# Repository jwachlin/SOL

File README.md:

# SOL
Long-term solar intensity sensing

People considering a photovoltaic installation on their property should be able to make a data-driven decision about the viability of such a system. While projects such as Google's Project Sunroof can provide large-scale estimates of solar intensity from satellite images, SOL will be able to provide data that incorporates local effects such as roof slope and direction, tree cover, or obstruction from nearby buildings.

See project logs for SOL at the Hackaday project page: https://hackaday.io/project/158984-sol-long-term-solar-intensity-sensing

R2 included a variety of upgrades to lower cost and improve performance:

- ADC with PGA allows better measurement accuracy (ESP32 ADC is highly nonlinear)
- Temperature sensor added (ESP32 internal temperature sensor has very poor performance)
- RTC added for accurate time monitoring without connecting to network
- Smaller PCB with smaller battery (14500 battery)
- Fixed dimensions and location of mounting hole (V1 didn't fit well in case)
- Easier programming by moving required pins to pin headers

However, R2 had some issues:

- Mistake on trace routing held temperature sensor output to ground, making it not work
- Forgot to add load capacitors on RTC crystal, so RTC does not work
- PCB vias not covered with soldermask underneath battery connectors, which would cause shorts
- The charger IC has a large pad underneath it, which was not included in its Eagle part
- The battery silkscreen was left on top of the PCB, when it should have been on the bottom. Not a functional issue, since battery connectors can be attached through either side
- Decoupling capacitor was not put near the ADC, when it should have been. The ADC still seems to work fine, but this should still be fixed

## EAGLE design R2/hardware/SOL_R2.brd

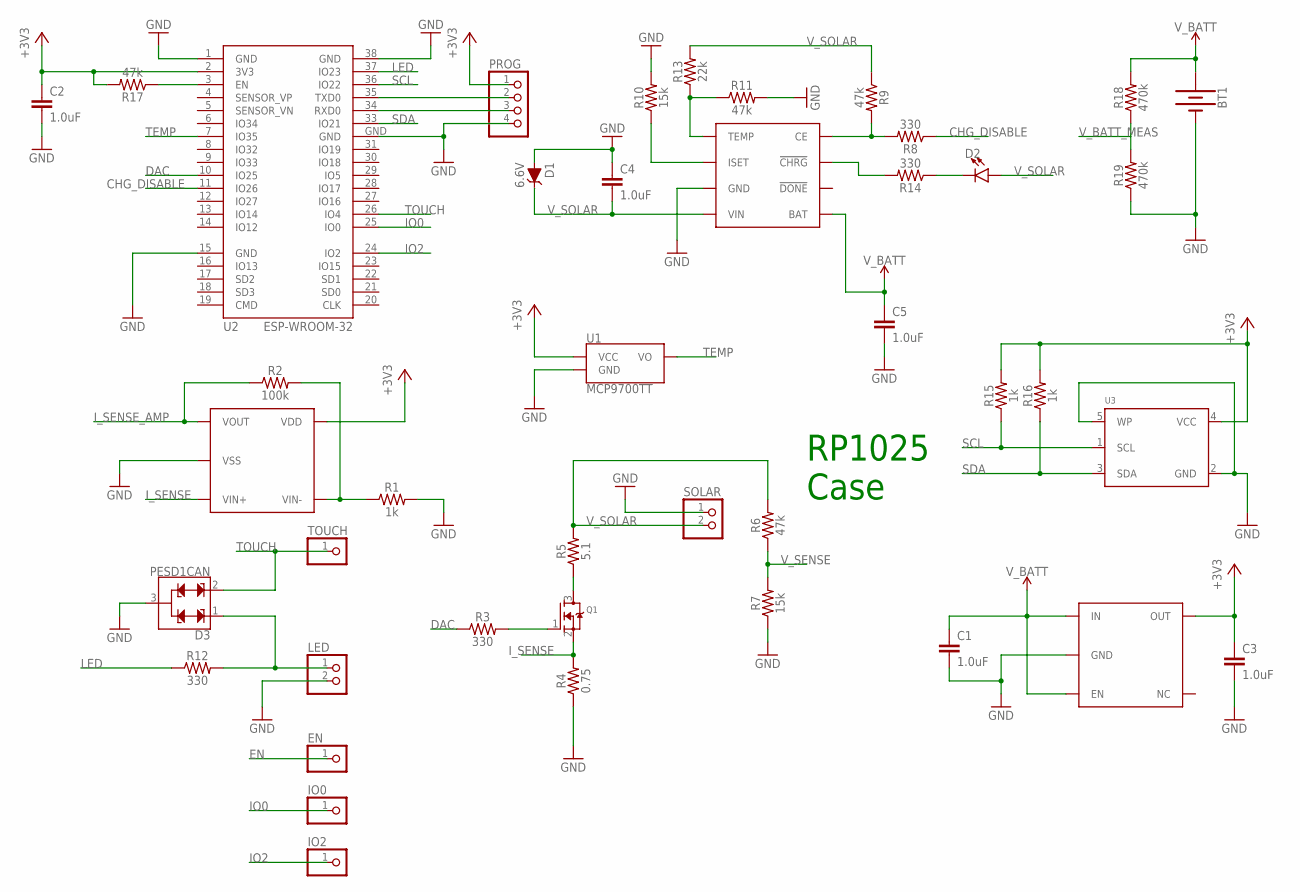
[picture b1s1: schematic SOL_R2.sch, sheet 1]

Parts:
BT1: BATTERY-AA
C1, C2, C3, C4, C5: 1.0uF; 0805
D1: 6.6V; SOD-323
D2: LED0603; LED-0603
D3: PESD1CAN; SOT23-3
EN: PINHD-1X1; 1X01
IO0, IO2: PINHD-1X1; 1X01
LED: PINHD-1X2; 1X02
PROG: PINHD-1X4; 1X04
Q1: MOSFET-NREFLOW; SOT23-R
R1, R15, R16: 1k; 0603
R2: 100k; 0603
R3, R8, R12, R14: 330; 0603
R4: 0.75; 0805
R5: 5.1; 0603
R6, R9, R11, R17: 47k; 0603
R7, R10: 15k; 0603
R13: 22k; 0603
R18, R19: 470k; 0603
SOLAR: PINHD-1X2; 1X02
TOUCH: PINHD-1X1; 1X01
U1: MCP9700TT; SOT23-3
U2: ESP-WROOM-32
U3: EEPROM_I2C_MCP24AA32; SOT23-5
U5: MCP6001; SOT23-5L
U6: TLV755; SOT23-DBV
U7: DIO5158XM8; MSOP8

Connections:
+3V3: C2.1, C3.1, PROG.1, R15.2, R16.2, R17.2, U1.1 (VCC), U2.2 (3V3), U3.4 (VCC), U5.5 (VDD), U6.5 (OUT); also elsewhere on the board
CHG_DISABLE: R8.1, U2.11 (IO26)
DAC: R3.1, U2.10 (IO25)
EN: EN.1, R17.1, U2.3 (EN)
GND: BT1.GND@1 (-), C1.2, C2.2, C3.2, C4.1, C5.2, D1.A, D3.3, LED.2, PROG.4, R1.2, R4.1, R7.1, R10.2, R11.2, R19.1, SOLAR.1, U1.3 (GND), U2.1 (GND), U2.15 (GND), U2.38 (GND), U2.GND, U3.2 (GND), U3.5 (WP), U5.2 (VSS), U6.2 (GND), U7.3 (GND); also elsewhere on the board
IO0: IO0.1, U2.25 (IO0)
IO2: IO2.1, U2.24 (IO2)
I_SENSE: Q1.2 (S), R4.2, U5.3 (VIN+)
I_SENSE_AMP: R2.1, U5.1 (VOUT); also elsewhere on the board
LED: R12.1, U2.37 (IO23)
unnamed: R10.1, U7.2 (ISET)
unnamed: D3.1, LED.1, R12.2
unnamed: R11.1, R13.1, U7.1 (TEMP)
unnamed: Q1.1 (G), R3.2
unnamed: R1.1, R2.2, U5.4 (VIN-)
unnamed: Q1.3 (D), R5.1
unnamed: R8.2, R9.2, U7.8 (CE)
unnamed: R14.2, U7.7 (!CHRG!)
unnamed: D2.C, R14.1
RXD: PROG.3, U2.34 (RXD0)
SCL: R15.1, U2.36 (IO22), U3.1 (SCL); also elsewhere on the board
SDA: R16.1, U2.33 (IO21), U3.3 (SDA); also elsewhere on the board
TEMP: U1.2 (VO), U2.7 (IO35)
TOUCH: D3.2, TOUCH.1, U2.26 (IO4)
TXD: PROG.2, U2.35 (TXD0)
V_BATT: BT1.PWR@1 (+), C1.1, C5.1, R18.2, U6.1 (IN), U6.3 (EN), U7.5 (BAT)
V_BATT_MEAS: R18.1, R19.2; also elsewhere on the board
V_SENSE: R6.1, R7.2; also elsewhere on the board
V_SOLAR: C4.2, D1.C, D2.A, R5.2, R6.2, R9.1, R13.2, SOLAR.2, U7.4 (VIN)

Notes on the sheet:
RP1025 Case

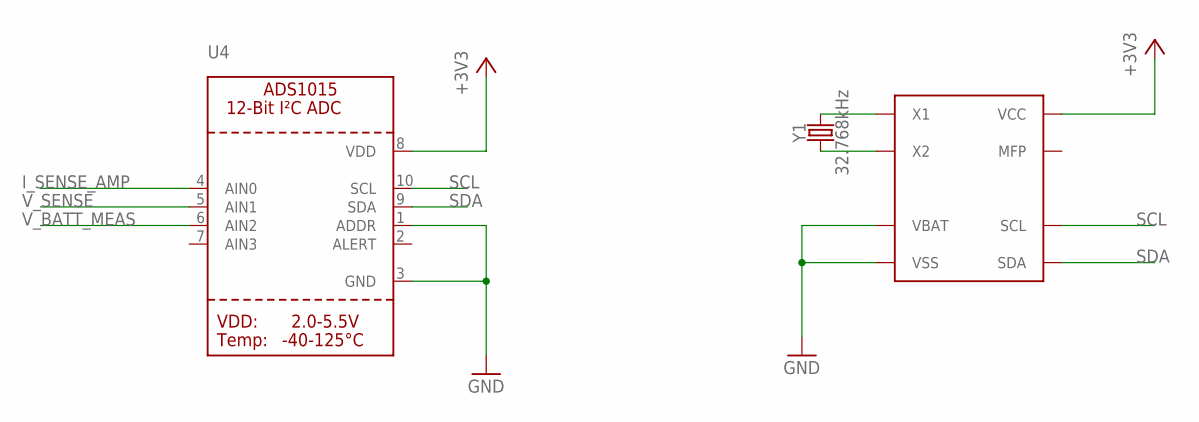
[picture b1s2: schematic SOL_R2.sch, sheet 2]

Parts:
U4: ADC_ADS1015; MSOP10
U8: MCP7940; MSOP8
Y1: 32.768kHz; CRYSTAL-SMD-3.2X1.5MM

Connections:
+3V3: U4.8 (VDD), U8.8 (VCC); also elsewhere on the board
GND: U4.1 (ADDR), U4.3 (GND), U8.3 (VBAT), U8.4 (VSS); also elsewhere on the board
I_SENSE_AMP: U4.4 (AIN0); also elsewhere on the board
unnamed: U8.1 (X1), Y1.P$2 (2)
unnamed: U8.2 (X2), Y1.P$1 (1)
SCL: U4.10 (SCL), U8.6 (SCL); also elsewhere on the board
SDA: U4.9 (SDA), U8.5 (SDA); also elsewhere on the board
V_BATT_MEAS: U4.6 (AIN2); also elsewhere on the board
V_SENSE: U4.5 (AIN1); also elsewhere on the board

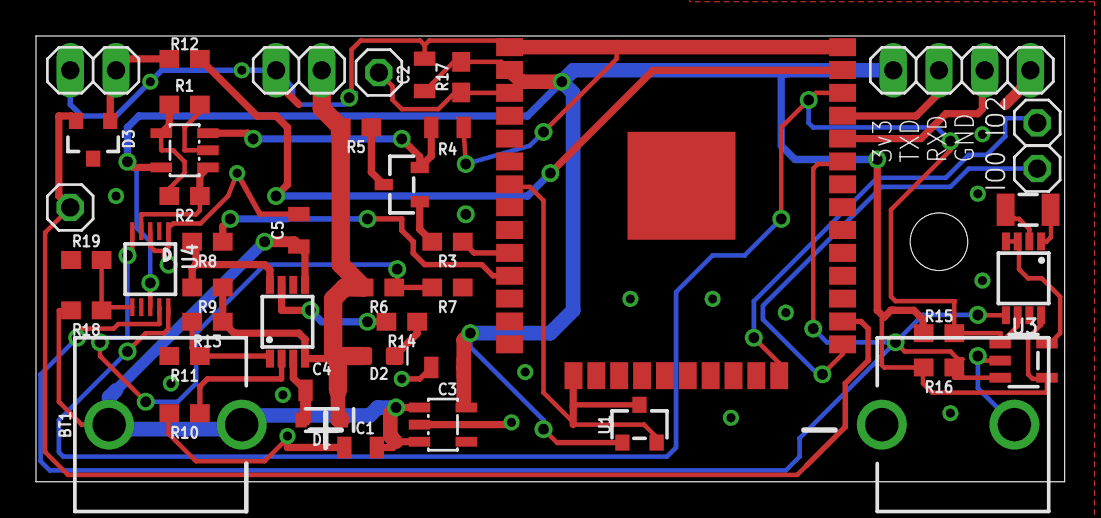
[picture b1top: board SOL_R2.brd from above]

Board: 2 copper layers, 57.1 x 24.8 mm, 45 parts (0 on the bottom side), 31 nets.

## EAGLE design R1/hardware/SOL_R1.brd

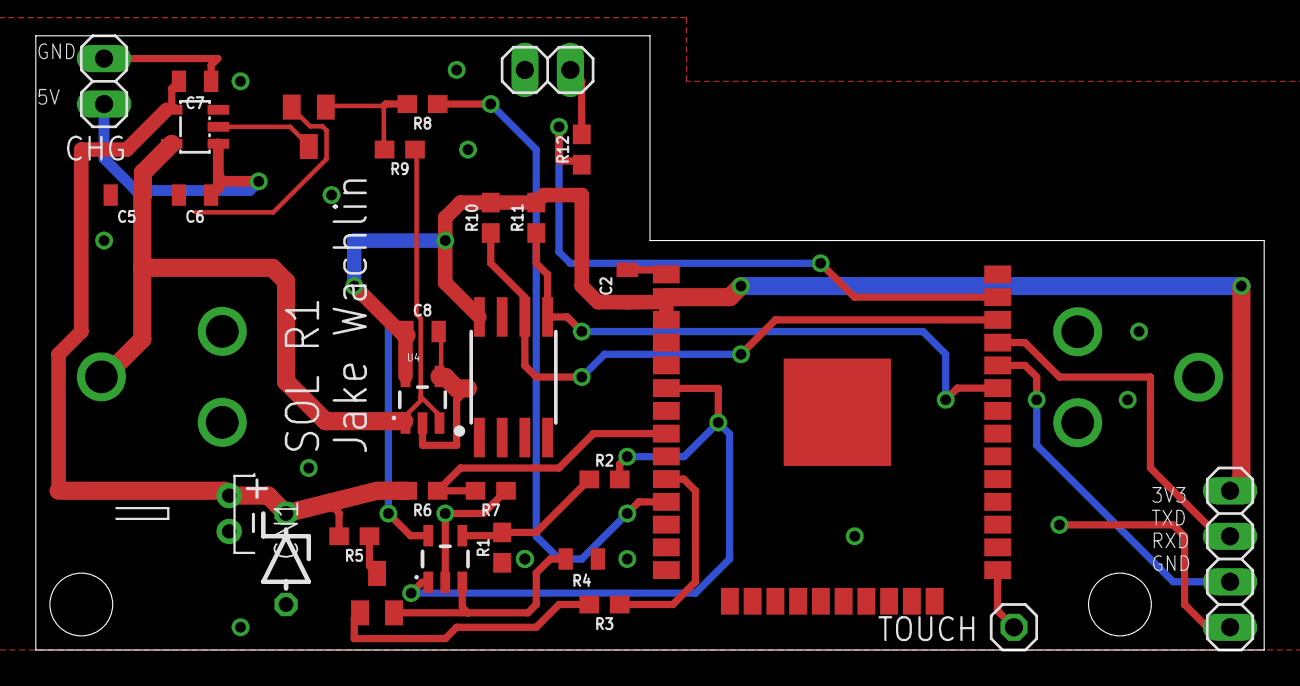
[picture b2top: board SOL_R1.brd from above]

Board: 2 copper layers, 68.6 x 34.3 mm, 31 parts (1 on the bottom side), 22 nets.

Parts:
BT1: BATTERY_18650-HOLDER
C2, C5, C6, C7, C8: 1.0uF; 0805
CHG: 1X02
CN1: JST-PH-2-THM-RA
D2: 7.5V; ZDIO-5
IC1: MAX1555; SOT23-5L
LED: 1X02
PROG: 1X04
Q2, Q3: SOT23
R1: 1k; 0603
R2: 100k; 0603
R3, R8, R12: 330; 0603
R4: 0.75; 0805
R5: 5.1; 0603
R6, R9: 47k; 0603
R7: 15k; 0603
R10, R11: 4.7k; 0603
TOUCH: 1X01
U2: ESP-WROOM-32
U3: I2C EEPROM; SO08-EIAJ
U4: 3.3V/150mA; SOT23-5
U$1: OPA344; SOT23-5

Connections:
+3V3: C2.1, C8.1, PROG.1, R10.2, R11.2, U2.2, U2.3, U3.8, U4.5, U$1.5
+5V: C6.1, CHG.1, IC1.1
CHG_DISABLE: R8.1, U2.11
DAC: R3.1, U2.10
GND: BT1.GND@1, C2.2, C5.2, C6.2, C7.1, C8.2, CHG.2, CN1.2, D2.A, LED.2, PROG.4, Q2.2, R1.1, R4.1, R7.1, U2.1, U2.15, U2.38, U2.GND, U3.1, U3.2, U3.3, U3.4, U3.7, U4.2, U4.4, U$1.2
I_SENSE: Q3.2, R4.2, U$1.3
I_SENSE_AMP: R2.2, U2.6, U$1.1
LED: R12.1, U2.37
unnamed: R1.2, R2.1, U$1.4
unnamed: LED.1, R12.2
unnamed: Q3.1, R3.2
unnamed: IC1.2, Q2.3
unnamed: Q3.3, R5.1
unnamed: Q2.1, R8.2, R9.2
RXD: PROG.3, U2.34
SCL: R10.1, U2.36, U3.6
SDA: R11.1, U2.33, U3.5
TOUCH: TOUCH.1, U2.25
TXD: PROG.2, U2.35
V_BATT: BT1.PWR@1, C5.1, IC1.5, R9.1, U4.1, U4.3
V_SENSE: R6.1, R7.2, U2.8
V_SOLAR: C7.2, CN1.1, D2.C, IC1.4, R5.2, R6.2

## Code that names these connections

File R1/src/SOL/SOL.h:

/*
MIT License

Copyright (c) 2018 by Jacob Wachlin

Permission is hereby granted, free of charge, to any person obtaining a copy
of this software and associated documentation files (the "Software"), to deal
in the Software without restriction, including without limitation the rights
to use, copy, modify, merge, publish, distribute, sublicense, and/or sell
copies of the Software, and to permit persons to whom the Software is
furnished to do so, subject to the following conditions:

The above copyright notice and this permission notice shall be included in all
copies or substantial portions of the Software.

THE SOFTWARE IS PROVIDED "AS IS", WITHOUT WARRANTY OF ANY KIND, EXPRESS OR
IMPLIED, INCLUDING BUT NOT LIMITED TO THE WARRANTIES OF MERCHANTABILITY,
FITNESS FOR A PARTICULAR PURPOSE AND NONINFRINGEMENT. IN NO EVENT SHALL THE
AUTHORS OR COPYRIGHT HOLDERS BE LIABLE FOR ANY CLAIM, DAMAGES OR OTHER
LIABILITY, WHETHER IN AN ACTION OF CONTRACT, TORT OR OTHERWISE, ARISING FROM,
OUT OF OR IN CONNECTION WITH THE SOFTWARE OR THE USE OR OTHER DEALINGS IN THE
SOFTWARE.
*/

/**
 * @file SOL.h
 * @author Jacob Wachlin
 * @date 22 June 2018
 * @brief SOL arduino compatible library for the ESP32
 */


#ifndef SOL_h
#define SOL_h

//#define SOL_DEBUG

//Define I2C addresses
#define EEPROM_ADDRESS 									0x50				// I2C EEPROM address

//Pins
#define LED_PIN											5//23					
#define CHG_DISABLE_PIN									26
#define SDA_PIN											21
#define SCL_PIN											22					
#define DAC_PIN              							25
#define V_SENSE_PIN          							32
#define I_SENSE_PIN          							34
#define TOUCH_PIN										T0// T1 //T1 is pin0, T1 is pin 4
#define DAC_RANGE            							255
#define ADC_RANGE            							4095
#define V_SENSE_RANGE        							3.9					// ESP32 ADC max voltage
#define I_SENSE_RANGE        							3.9					// ESP32 ADC max voltage
#define I_SENSE_AMPLIFICATION							101.0				// Amplification stage for current sensing
#define R_SENSE              							0.75				// Current sense resistance, Ohms

#define EEPROM_ADDRESS_WIFI_CREDENTIALS_AVAILABLE		0x0000				// Location for flag if WiFi credentials have been sent
#define EEPROM_ADDRESS_WIFI_SSID_START					0x0001				// Location of start of WiFi SSID
#define EEPROM_ADDRESS_WIFI_SSID_END					0x0041				// Location of end of WiFi SSID
#define EEPROM_ADDRESS_WIFI_PSWD_START					0x0042				// Location of start of WiFi password
#define EEPROM_ADDRESS_WIFI_PSWD_END					0x006A				// Location of end of WiFi password
#define EEPROM_ADDRESS_WIFI_SSID_LENGTH					0x006B				// Location of length of WiFi SSID length (# of chars)
#define EEPROM_ADDRESS_WIFI_PSWD_LENGTH					0x006C				// Location of length of WiFi PSWD length (# of chars)
#define EEPROM_ADDRESS_LAST_STORAGE_ADDRESS				0x006D				// Location of information about where data was stored last (also takes 0x006E)
#define EEPROM_ADDRESS_DATA_RANGE_START_ADDRESS 		0x006F				// Location of start of data address
#define EEPROM_ADDRESS_DATA_RANGE_END_ADDRESS 			0x4000				// Last location available in 128kbit EEPROM

#define SLEEP_TIME_SECONDS								300 //600			// Amount of time to sleep between sensing
#define SENSE_COUNT_TO_SEND								2					// Number of sensing datapoints before upload
#define PROVISION_TIMEOUT								600					// WiFi provisioning timeout

// Only charge in certain temperature range
#define CHARGE_TEMP_MIN_CELSIUS							0
#define CHARGE_TEMP_MAX_CELSIUS							45

/**
 * @brief Data packet generated by SOL during each sensing cycle
 */
typedef struct data_packet_t
{
	uint32_t timestamp;
	float peak_power_mW;
	float peak_current_mA;
	float peak_voltage_V;
	float temp_celsius;
	uint32_t ID;
} data_packet_t;

/**
 * @brief Performs initialization for SOL
 *
 * 	This function setups up GPIO, I2C, and touch sensor interrupt
 */
void SOL_begin();

/**
 * @brief Manages SOL task upon wakeup, triggering data reading and uploading when necessary
 *
 */
void SOL_task();

/**
 * @brief Checks in EEPROM if  WiFi credentials are available and loads them if so
 *
 * @return 1 if credentials are available, otherwise 0
 */
uint8_t SOL_hasWiFiCredentials();

/**
 * @brief Attempts to connect to Wifi
 *
 * @param timeout The connection attempt timeout in seconds
 *
 * @return 1 if connected, otherwise 0
 */
uint8_t SOL_connectToWiFi(uint16_t timeout);

/**
 * @brief Handles provisioning to WiFi network by putting ESP32 into softAP mode
 */
void SOL_startProvisioning(void);

/**
 * @brief Uploads all available data from EEPROM
 *
 */
void SOL_upload(void);

/**
 * @brief Places system into deep sleep, enabling charging if temperature in valid range
 *
 * @param len The time to sleep in seconds
 *
 */
void SOL_deepsleep(int len);	

/**
 * @brief Generates a new data packet from sensors
 *
 */
void SOL_generateDataPacket(void);

/**
 * @brief Gets data packet stored in EEPROM
 *
 * @param start_address The starting location for the data packet struct
 *
 * @return The data packet
 *
 */
data_packet_t SOL_getDataPacket(uint16_t start_address);

/**
 * @brief Uploads an individual data packet
 *
 * @param data Pointer to data packet to upload
 *
 */
void SOL_uploadDataPacket(data_packet_t * data);

/**
 * @brief Handles touch sensor input by setting a flag
 *
 */
static void SOL_handletouch(void);

/**
 * @brief Writes a single byte to EEPROM
 *
 * @param address The address in EEPROM to write to
 * @param data The data to put into EEPROM
 *
 */
void SOL_writeEEPROMByte(uint16_t address, uint8_t data);

/**
 * @brief Abstract method for writing N bytes of data to EEPROM
 *
 * @param address The starting address in EEPROM to write to
 * @param data Pointer to the data
 * @param size The number of bytes to write
 *
 */
void SOL_writeEEPROMNByte(uint16_t address, uint8_t * data, uint16_t size);

/**
 * @brief Reads a single byte of data from EEPROM
 *
 * @param address The address in EEPROM of the byte to read
 *
 * @return The byte from EEPROM
 *
 */
uint8_t SOL_readEEPROMByte(uint16_t address);

/**
 * @brief Abstract method for reading N bytes of data from EEPROM
 *
 * @param address The starting address in EEPROM to read from
 * @param data Pointer to the data storage to read data into
 * @param size The number of bytes to read
 *
 */
void SOL_readEEPROMNByte(uint16_t address, uint8_t * data, uint16_t size);

#endif

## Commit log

2018-06-23 Added hardware files and BoM for first version
2018-06-23 Adds Arduino ESP32 compatible library for SOL
2018-06-24 Remove unneeded delays to lower power. Use WiFiManager for provision
    WiFiManager library handles wifi provisioning, automatically presenting available networks. I2C speed increased to 400 kHz and unnecessary delays were removed, so system is awake for shorter times, l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
2018-11-03 Rearranges repo. Adds V2 design documents and firmware. Updated readme about v2 issues

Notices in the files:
parts and their libraries:
esp32: Creative Commons Attribution-ShareAlike 4.0 International
SparkFun-Resistors: Licensing: Creative Commons ShareAlike 4.0 International - https://creativecommons.org/licenses/by-sa/4.0
